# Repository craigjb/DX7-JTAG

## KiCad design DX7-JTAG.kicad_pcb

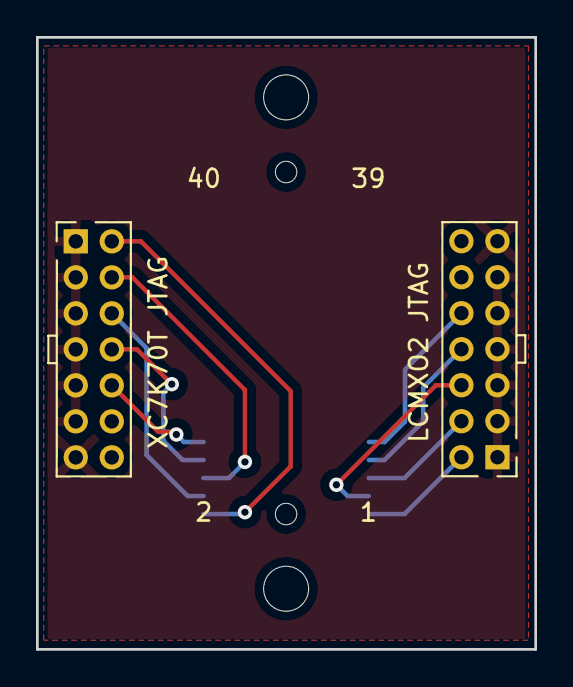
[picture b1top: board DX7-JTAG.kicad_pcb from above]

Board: 2 copper layers, 27.7 x 34.0 mm, 3 parts (1 on the bottom side), 11 nets.

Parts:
J2: DX7; SAMTEC_FSI-120-03-X-D-AD-TR
LCMXO2 JTAG: JTAG-LCMXO2; JTAG-Xilinx-2mm-Vert
XC7K70T JTAG: JTAG-XC7K70; JTAG-Xilinx-2mm-Vert

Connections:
/KTCK: J2.4, XC7K70T JTAG.6
/KTDI: J2.10, XC7K70T JTAG.10
/KTDO: J2.8, XC7K70T JTAG.8
/KTMS: J2.6, XC7K70T JTAG.4
/KVREF: J2.2, XC7K70T JTAG.2
/LTCK: J2.3, LCMXO2 JTAG.6
/LTDI: J2.9, LCMXO2 JTAG.10
/LTDO: J2.7, LCMXO2 JTAG.8
/LTMS: J2.5, LCMXO2 JTAG.4
/LVREF: J2.1, LCMXO2 JTAG.2
GND: J2.12, J2.40, LCMXO2 JTAG.1, LCMXO2 JTAG.3, LCMXO2 JTAG.5, LCMXO2 JTAG.7, LCMXO2 JTAG.9, LCMXO2 JTAG.11, LCMXO2 JTAG.13, XC7K70T JTAG.1, XC7K70T JTAG.3, XC7K70T JTAG.5, XC7K70T JTAG.7, XC7K70T JTAG.9, XC7K70T JTAG.11, XC7K70T JTAG.13

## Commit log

2020-12-30 Add license
